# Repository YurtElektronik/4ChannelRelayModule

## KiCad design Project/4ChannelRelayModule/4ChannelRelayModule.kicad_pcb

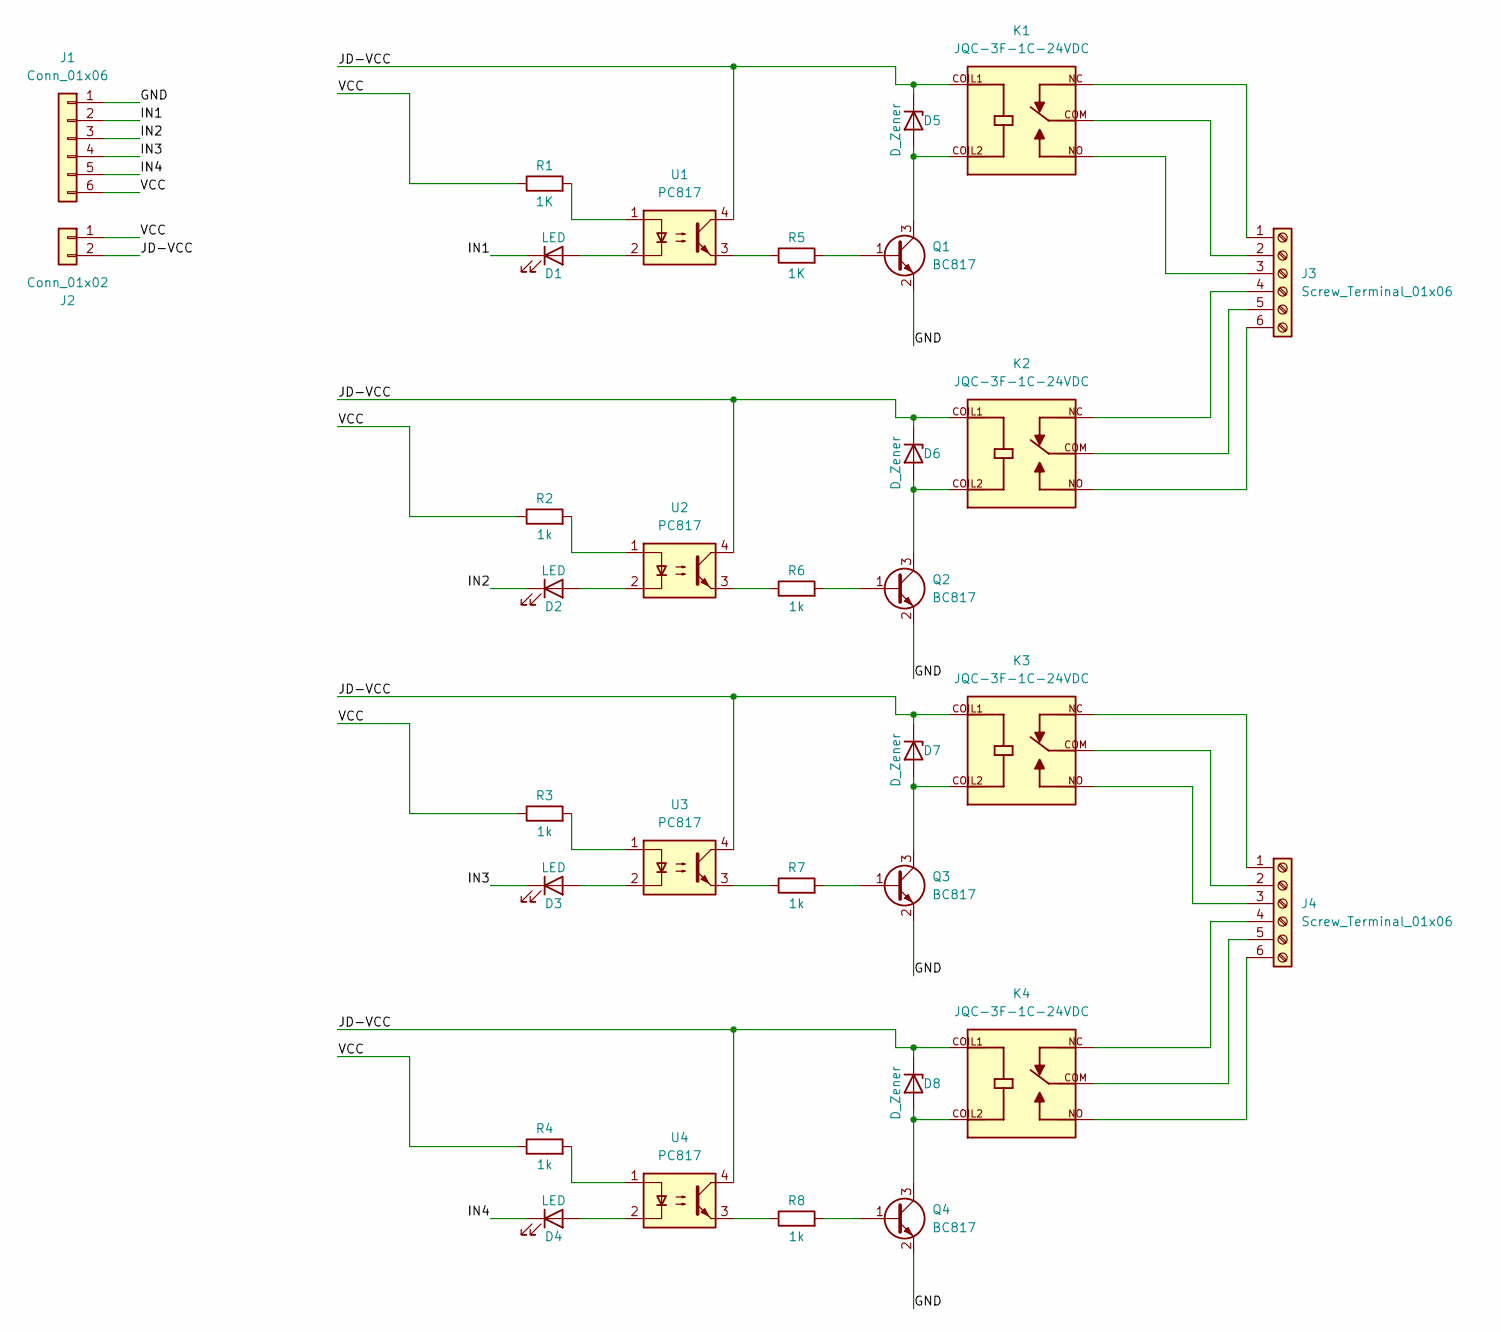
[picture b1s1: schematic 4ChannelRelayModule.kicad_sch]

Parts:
D1, D2, D3, D4: LED; LED_0805_2012Metric
D5, D6, D7, D8: D_Zener; Nexperia_CFP3_SOD-123W
J1: Conn_01x06; PinHeader_1x06_P2.54mm_Vertical
J2: Conn_01x02; PinHeader_1x02_P2.54mm_Vertical
J3, J4: Screw_Terminal_01x06; TerminalBlock_RND_205-00016_1x06_P5.00mm_Horizontal
K1, K2, K3, K4: JQC-3F-1C-24VDC; RELAY_JQC-3F-1C-24VDC; PARTREV N/A
Q1, Q2, Q3, Q4: BC817; SOT-23
R1, R5: 1K; R_0805_2012Metric
R2, R3, R4, R6, R7, R8: 1k; R_0805_2012Metric
U1, U2, U3, U4: PC817; SOIC254P1016X390-4N

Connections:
/GND: J1.1, Q1.2 (E), Q2.2 (E), Q3.2 (E), Q4.2 (E)
/IN1: D1.1 (K), J1.2
/IN2: D2.1 (K), J1.3
/IN3: D3.1 (K), J1.4
/IN4: D4.1 (K), J1.5
/JD-VCC: D5.1 (K), D6.1 (K), D7.1 (K), D8.1 (K), J2.2, K1.COIL1, K2.COIL1, K3.COIL1, K4.COIL1, U1.4, U2.4, U3.4, U4.4
/VCC: J1.6, J2.1, R1.1, R2.1, R3.1, R4.1
unnamed: D1.2 (A), U1.2
unnamed: D2.2 (A), U2.2
unnamed: D3.2 (A), U3.2
unnamed: D4.2 (A), U4.2
unnamed: D5.2 (A), K1.COIL2, Q1.3 (C)
unnamed: D6.2 (A), K2.COIL2, Q2.3 (C)
unnamed: D7.2 (A), K3.COIL2, Q3.3 (C)
unnamed: D8.2 (A), K4.COIL2, Q4.3 (C)
unnamed: J3.1, K1.NC
unnamed: J3.4, K2.NC
unnamed: J4.1, K3.NC
unnamed: J4.3, K3.NO
unnamed: J4.4, K4.NC
unnamed: J4.5, K4.COM
unnamed: J4.6, K4.NO
unnamed: J3.2, K1.COM
unnamed: J3.3, K1.NO
unnamed: J3.5, K2.COM
unnamed: J3.6, K2.NO
unnamed: J4.2, K3.COM
unnamed: Q1.1 (B), R5.2
unnamed: Q2.1 (B), R6.2
unnamed: Q3.1 (B), R7.2
unnamed: Q4.1 (B), R8.2
unnamed: R1.2, U1.1
unnamed: R2.2, U2.1
unnamed: R3.2, U3.1
unnamed: R4.2, U4.1
unnamed: R5.1, U1.3
unnamed: R6.1, U2.3
unnamed: R7.1, U3.3
unnamed: R8.1, U4.3

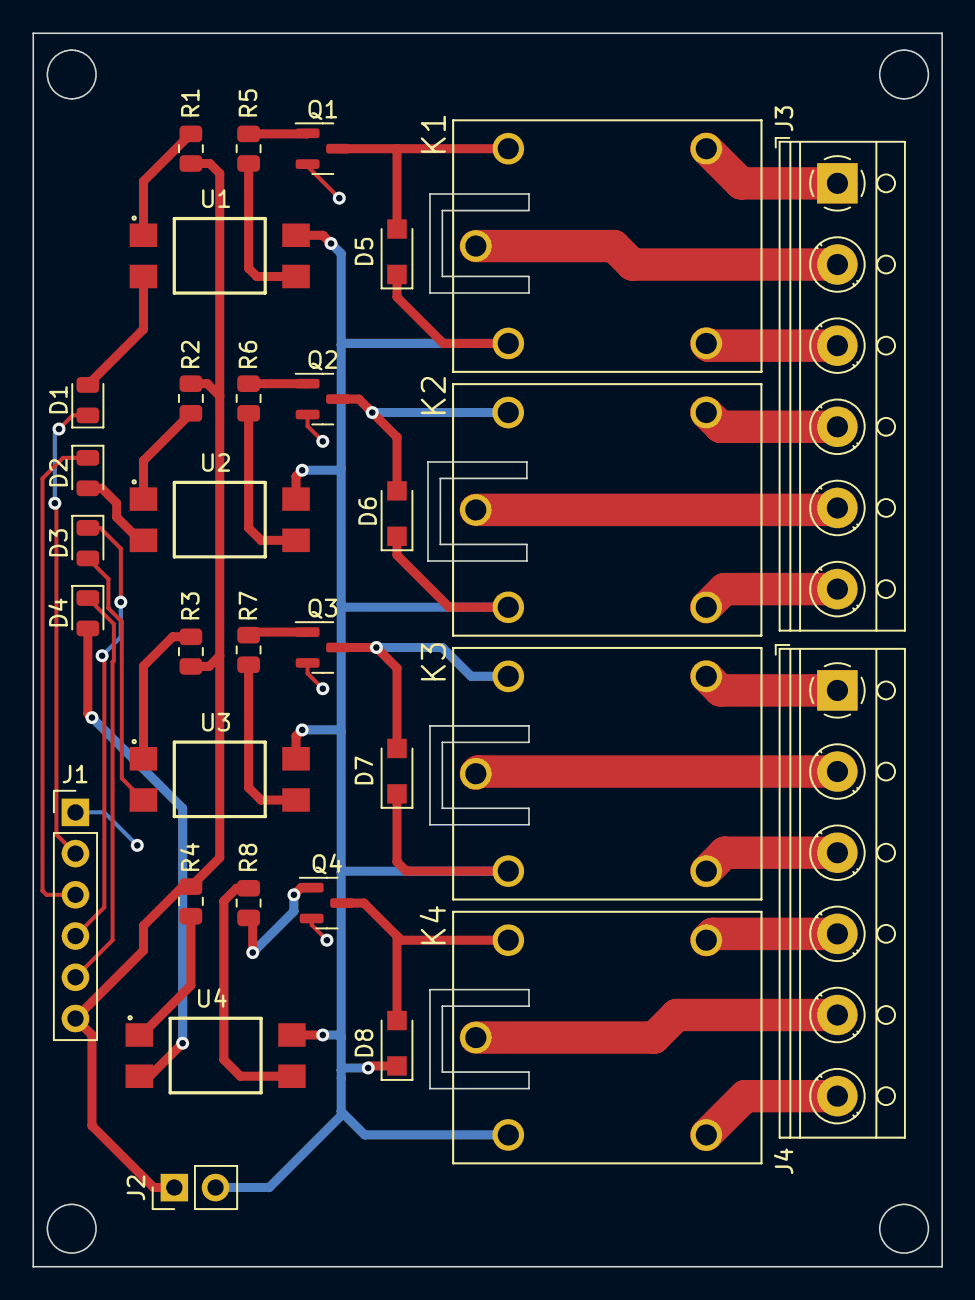
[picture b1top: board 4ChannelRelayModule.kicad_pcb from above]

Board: 2 copper layers, 56.0 x 76.0 mm, 32 parts (0 on the bottom side), 39 nets.

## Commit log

2022-12-13 Datasheet
2022-12-13 4ChannelRelayModule
2022-12-13 FD
    FD
2022-12-18 Sunum
2023-01-20 012023
2023-01-27 last
